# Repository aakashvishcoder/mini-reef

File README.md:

# Mini-Reef FPGA Board

A low-cost 4-layer Artix-7 board that runs a small Reef-style accelerator against real HyperRAM, and measures bandwidth, latency and tokens per second. A CH32V307 board acts as the test host.

- FPGA: XC7A15T-FTG256 (footprint-compatible with XC7A35T)
- Memory: Winbond W958D8NBYA5I, 256 Mb HyperRAM on a 1.8 V bank
- USB-C: power, plus CH347T for USB-JTAG and console
- Manufacturing: JLCPCB 4-layer, assembled

## Layout

| Path | Contents |
|---|---|
| `schematic-guide/` | Section-by-section schematic guides |
| `planning-BOM.csv` | Planning BOM with LCSC numbers (not the JLC upload format) |
| `mini-reef.pretty/` | Project footprints not in KiCad's stock library |
| `mini-reef.kicad_sym` | Project symbols: CH347T, W958D8NBYA HyperRAM |
| `fp-lib-table`, `sym-lib-table` | Register the project libraries |

## Schematic sections

| # | Section | Main parts |
|---|---|---|
| 1 | USB-C & Power | USB-C, fuse, 3x TPS62130A (1.0 / 1.8 / 3.3 V, sequenced) |
| 2 | FPGA Power | XC7A15T unit D, UG483 decoupling |
| 3 | HyperRAM | W958D8NBYA5I on bank 35 (1.8 V), debug pins on bank 34 |
| 4 | USB-JTAG & Console | CH347T (mode 3), JTAG header, bank 0 config straps |
| 5 | Clock & Config | 50 MHz oscillator, W25Q32 flash, banks 14/15 |
| 6 | Test Host & Debug | CH32V307 link header, debug header, LEDs, button |

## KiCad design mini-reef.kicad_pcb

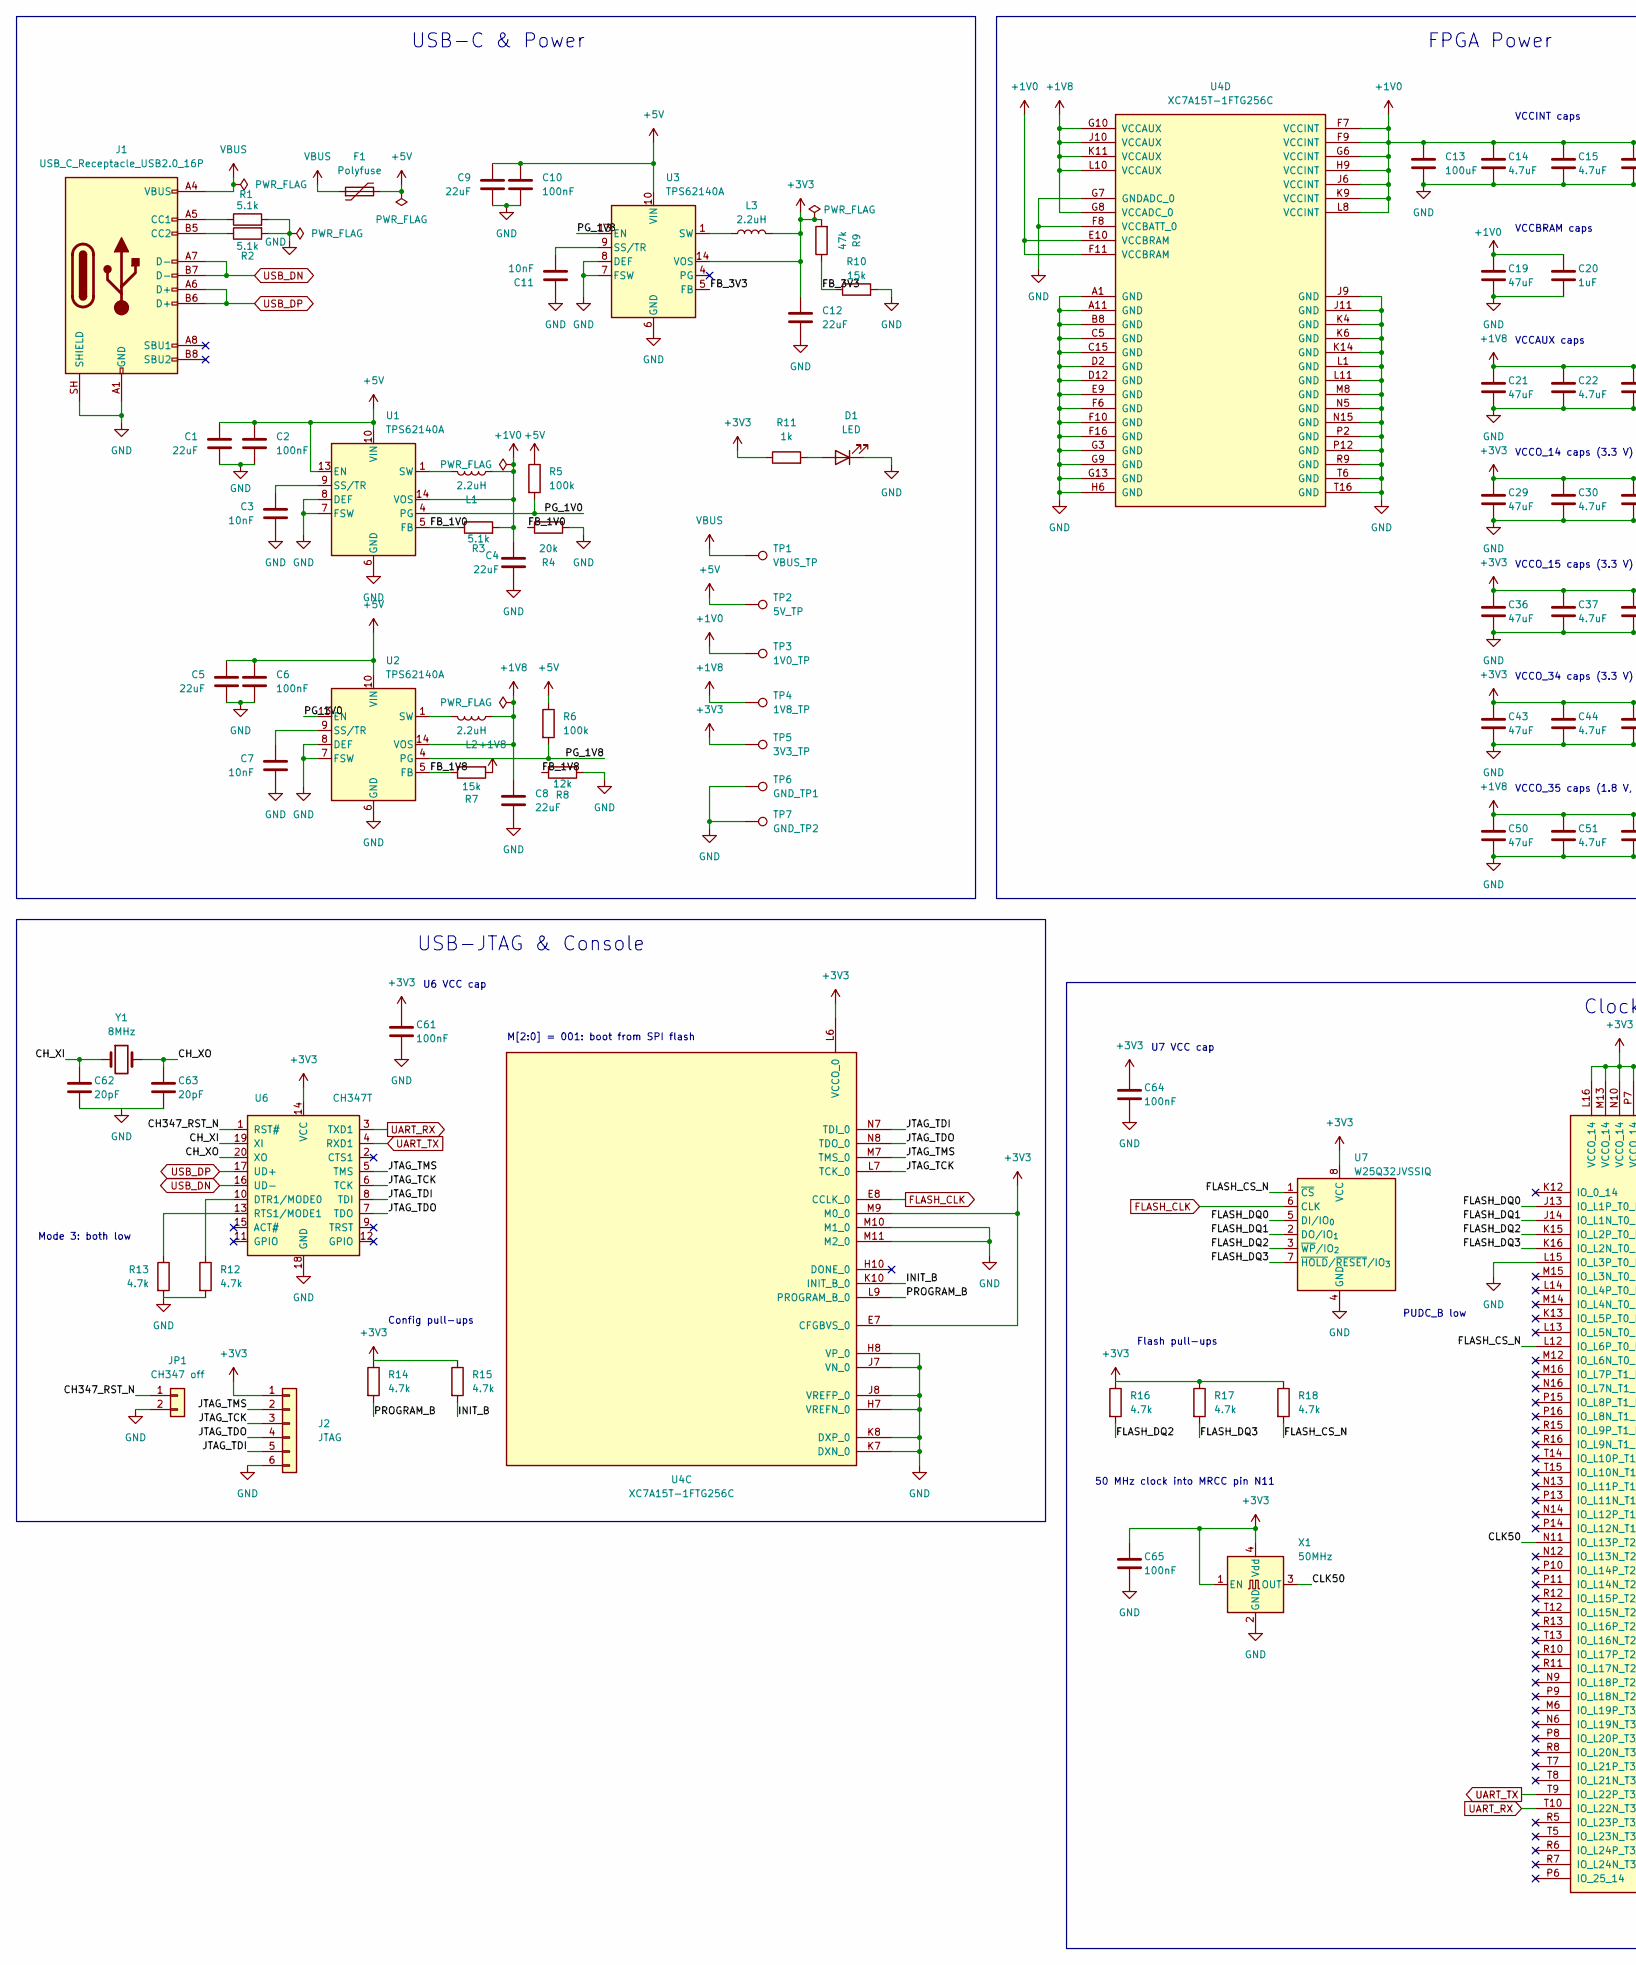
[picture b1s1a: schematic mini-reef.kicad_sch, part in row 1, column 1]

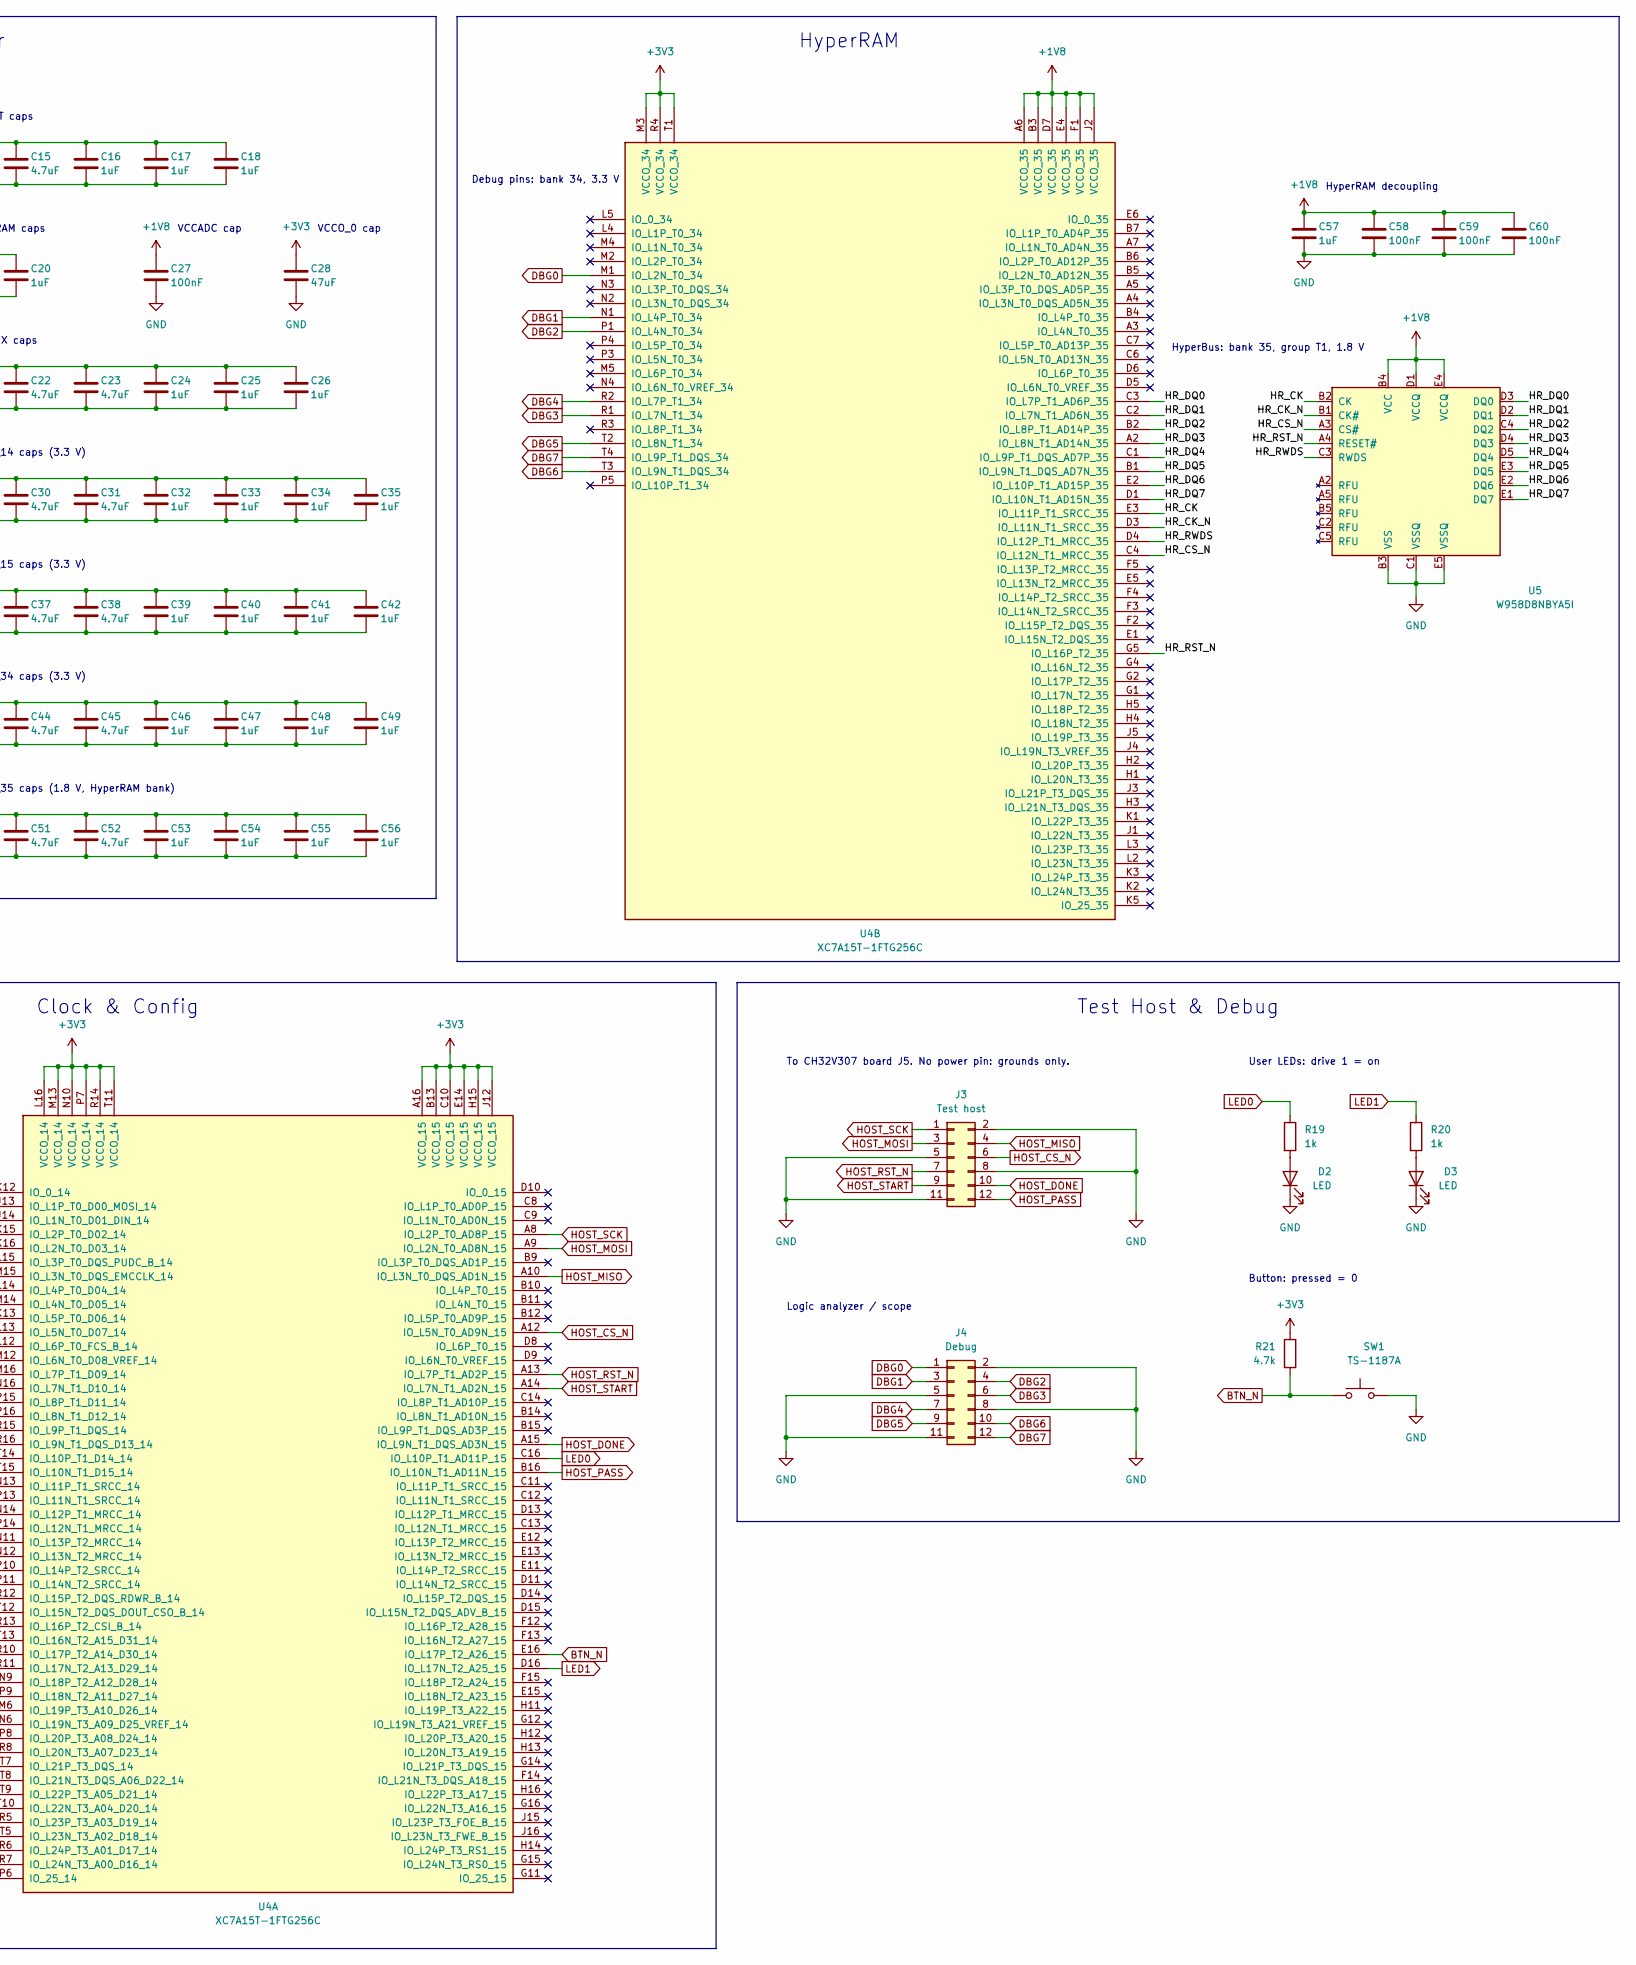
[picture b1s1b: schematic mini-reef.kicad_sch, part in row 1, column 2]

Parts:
C1, C4, C5, C8, C9, C12: 22uF; C_0805_2012Metric; LCSC C45783
C2, C6, C10, C27, C58, C59, C60, C61, C64, C65: 100nF; C_0402_1005Metric; LCSC C1525
C3, C7, C11: 10nF; C_0402_1005Metric; LCSC C15195
C13: 100uF; C_1206_3216Metric; LCSC C15008
C14, C15, C22, C23, C30, C31, C37, C38, C44, C45, C51, C52: 4.7uF; C_0805_2012Metric; LCSC C1779
C16, C17, C18, C20, C24, C25, C26, C32, C33, C34, C35, C39, C40, C41, C42, C46, C47, C48, C49, C53, C54, C55, C56, C57: 1uF; C_0402_1005Metric; LCSC C52923
C19, C21, C28, C29, C36, C43, C50: 47uF; C_1206_3216Metric; LCSC C96123
C62, C63: 20pF; C_0402_1005Metric; LCSC C1554
D1, D2, D3: LED; LED_0603_1608Metric; LCSC C2286
F1: Polyfuse; Fuse_1206_3216Metric; LCSC C20801
J1: USB_C_Receptacle_USB2.0_16P; USB_C_Receptacle_HRO_TYPE-C-31-M-12; LCSC C165948
J2: JTAG; PinHeader_1x06_P2.54mm_Vertical
J3: Test host; PinHeader_2x06_P2.54mm_Vertical
J4: Debug; PinHeader_2x06_P2.54mm_Vertical
JP1: CH347 off; PinHeader_1x02_P2.54mm_Vertical
L1, L2, L3: 2.2uH; IND-SMD_L4.5-W4.1_SRP4020TA; LCSC C719179
R1, R2, R3: 5.1k; R_0402_1005Metric; LCSC C25905
R4: 20k; R_0402_1005Metric; LCSC C25765
R5, R6: 100k; R_0402_1005Metric; LCSC C25741
R7, R10: 15k; R_0402_1005Metric; LCSC C25756
R8: 12k; R_0402_1005Metric; LCSC C25752
R9: 47k; R_0402_1005Metric; LCSC C25792
R11, R19, R20: 1k; R_0402_1005Metric; LCSC C11702
R12, R13, R14, R15, R16, R17, R18, R21: 4.7k; R_0402_1005Metric; LCSC C25900
SW1: TS-1187A; SW_Push_1P1T_XKB_TS-1187A; LCSC C318884
TP1: VBUS_TP; TestPoint_Pad_D1.5mm
TP2: 5V_TP; TestPoint_Pad_D1.5mm
TP3: 1V0_TP; TestPoint_Pad_D1.5mm
TP4: 1V8_TP; TestPoint_Pad_D1.5mm
TP5: 3V3_TP; TestPoint_Pad_D1.5mm
TP6: GND_TP1; TestPoint_Pad_D1.5mm
TP7: GND_TP2; TestPoint_Pad_D1.5mm
U1, U2, U3: TPS62140A; VQFN-16-1EP_3x3mm_P0.5mm_EP1.68x1.68mm_ThermalVias; LCSC C129366
U4: XC7A15T-1FTG256C; Xilinx_FTG256; LCSC C1521788
U5: W958D8NBYA5I; BGA-24_6x8mm_Layout5x5_P1.0mm; LCSC C7420405
U6: CH347T; TSSOP-20_4.4x6.5mm_P0.65mm; LCSC C5122332
U7: W25Q32JVSSIQ; SOIC-8_5.3x5.3mm_P1.27mm; LCSC C179173
X1: 50MHz; Oscillator_SMD_Abracon_ASE-4Pin_3.2x2.5mm; LCSC C717684
Y1: 8MHz; Crystal_SMD_5032-2Pin_5.0x3.2mm; LCSC C115962

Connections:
+1V0: C4.1, C13.1, C14.1, C15.1, C16.1, C17.1, C18.1, C19.1, C20.1, L1.2, R3.2, TP3.1, U1.14 (VOS), U4.E10 (VCCBRAM), U4.F7 (VCCINT), U4.F9 (VCCINT), U4.F11 (VCCBRAM), U4.G6 (VCCINT), U4.H9 (VCCINT), U4.J6 (VCCINT), U4.K9 (VCCINT), U4.L8 (VCCINT)
+1V8: C8.1, C21.1, C22.1, C23.1, C24.1, C25.1, C26.1, C27.1, C50.1, C51.1, C52.1, C53.1, C54.1, C55.1, C56.1, C57.1, C58.1, C59.1, C60.1, L2.2, R7.2, TP4.1, U2.14 (VOS), U4.A6 (VCCO_35), U4.B3 (VCCO_35), U4.D7 (VCCO_35), U4.E4 (VCCO_35), U4.F1 (VCCO_35), U4.G8 (VCCADC_0), U4.G10 (VCCAUX), U4.J2 (VCCO_35), U4.J10 (VCCAUX), U4.K11 (VCCAUX), U4.L10 (VCCAUX), U5.B4 (VCC), U5.D1 (VCCQ), U5.E4 (VCCQ)
+3V3: C12.1, C28.1, C29.1, C30.1, C31.1, C32.1, C33.1, C34.1, C35.1, C36.1, C37.1, C38.1, C39.1, C40.1, C41.1, C42.1, C43.1, C44.1, C45.1, C46.1, C47.1, C48.1, C49.1, C61.1, C64.1, C65.1, J2.1, L3.2, R9.2, R11.1, R14.1, R15.1, R16.1, R17.1, R18.1, R21.1, TP5.1, U3.14 (VOS), U4.A16 (VCCO_15), U4.B13 (VCCO_15), U4.C10 (VCCO_15), U4.E7 (CFGBVS_0), U4.E14 (VCCO_15), U4.H15 (VCCO_15), U4.J12 (VCCO_15), U4.L6 (VCCO_0), U4.L16 (VCCO_14), U4.M3 (VCCO_34), U4.M9 (M0_0), U4.M13 (VCCO_14), U4.N10 (VCCO_14), U4.P7 (VCCO_14), U4.R4 (VCCO_34), U4.R14 (VCCO_14), U4.T1 (VCCO_34), U4.T11 (VCCO_14), U6.14 (VCC), U7.8 (VCC), X1.1 (EN), X1.4 (Vdd)
+5V: C1.1, C2.1, C5.1, C6.1, C9.1, C10.1, F1.2, R5.1, R6.1, TP2.1, U1.10 (VIN), U1.11 (VIN), U1.12 (VIN), U1.13 (EN), U2.10 (VIN), U2.11 (VIN), U2.12 (VIN), U3.10 (VIN), U3.11 (VIN), U3.12 (VIN)
/CH347_RST_N: JP1.1, U6.1 (RST#)
/CH_XI: C62.1, U6.19 (XI), Y1.1
/CH_XO: C63.1, U6.20 (XO), Y1.2
/CLK50: U4.N11 (IO_L13P_T2_MRCC_14), X1.3 (OUT)
/FB_1V0: R3.1, R4.1, U1.5 (FB)
/FB_1V8: R7.1, R8.2, U2.5 (FB)
/FB_3V3: R9.1, R10.1, U3.5 (FB)
/FLASH_CS_N: R18.2, U4.L12 (IO_L6P_T0_FCS_B_14), U7.1 (~CS)
/FLASH_DQ0: U4.J13 (IO_L1P_T0_D00_MOSI_14), U7.5 (DI/IO_{0})
/FLASH_DQ1: U4.J14 (IO_L1N_T0_D01_DIN_14), U7.2 (DO/IO_{1})
/FLASH_DQ2: R16.2, U4.K15 (IO_L2P_T0_D02_14), U7.3 (~WP/IO_{2})
/FLASH_DQ3: R17.2, U4.K16 (IO_L2N_T0_D03_14), U7.7 (~HOLD/~RESET/IO_{3})
/HR_CK: U4.E3 (IO_L11P_T1_SRCC_35), U5.B2 (CK)
/HR_CK_N: U4.D3 (IO_L11N_T1_SRCC_35), U5.B1 (CK#)
/HR_CS_N: U4.C4 (IO_L12N_T1_MRCC_35), U5.A3 (CS#)
/HR_DQ0: U4.C3 (IO_L7P_T1_AD6P_35), U5.D3 (DQ0)
/HR_DQ1: U4.C2 (IO_L7N_T1_AD6N_35), U5.D2 (DQ1)
/HR_DQ2: U4.B2 (IO_L8P_T1_AD14P_35), U5.C4 (DQ2)
/HR_DQ3: U4.A2 (IO_L8N_T1_AD14N_35), U5.D4 (DQ3)
/HR_DQ4: U4.C1 (IO_L9P_T1_DQS_AD7P_35), U5.D5 (DQ4)
/HR_DQ5: U4.B1 (IO_L9N_T1_DQS_AD7N_35), U5.E3 (DQ5)
/HR_DQ6: U4.E2 (IO_L10P_T1_AD15P_35), U5.E2 (DQ6)
/HR_DQ7: U4.D1 (IO_L10N_T1_AD15N_35), U5.E1 (DQ7)
/HR_RST_N: U4.G5 (IO_L16P_T2_35), U5.A4 (RESET#)
/HR_RWDS: U4.D4 (IO_L12P_T1_MRCC_35), U5.C3 (RWDS)
/INIT_B: R15.2, U4.K10 (INIT_B_0)
/JTAG_TCK: J2.3, U4.L7 (TCK_0), U6.6 (TCK)
/JTAG_TDI: J2.5, U4.N7 (TDI_0), U6.8 (TDI)
/JTAG_TDO: J2.4, U4.N8 (TDO_0), U6.7 (TDO)
/JTAG_TMS: J2.2, U4.M7 (TMS_0), U6.5 (TMS)
/PG_1V0: R5.2, U1.4 (PG), U2.13 (EN)
/PG_1V8: R6.2, U2.4 (PG), U3.13 (EN)
/PROGRAM_B: R14.2, U4.L9 (PROGRAM_B_0)
BTN_N: R21.2, SW1.1, U4.E16 (IO_L17P_T2_A26_15)
DBG0: J4.1, U4.M1 (IO_L2N_T0_34)
DBG1: J4.3, U4.N1 (IO_L4P_T0_34)
DBG2: J4.4, U4.P1 (IO_L4N_T0_34)
DBG3: J4.6, U4.R1 (IO_L7N_T1_34)
DBG4: J4.7, U4.R2 (IO_L7P_T1_34)
DBG5: J4.9, U4.T2 (IO_L8N_T1_34)
DBG6: J4.10, U4.T3 (IO_L9N_T1_DQS_34)
DBG7: J4.12, U4.T4 (IO_L9P_T1_DQS_34)
FLASH_CLK: U4.E8 (CCLK_0), U7.6 (CLK)
GND: C1.2, C2.2, C3.2, C4.2, C5.2, C6.2, C7.2, C8.2, C9.2, C10.2, C11.2, C12.2, C13.2, C14.2, C15.2, C16.2, C17.2, C18.2, C19.2, C20.2, C21.2, C22.2, C23.2, C24.2, C25.2, C26.2, C27.2, C28.2, C29.2, C30.2, C31.2, C32.2, C33.2, C34.2, C35.2, C36.2, C37.2, C38.2, C39.2, C40.2, C41.2, C42.2, C43.2, C44.2, C45.2, C46.2, C47.2, C48.2, C49.2, C50.2, C51.2, C52.2, C53.2, C54.2, C55.2, C56.2, C57.2, C58.2, C59.2, C60.2, C61.2, C62.2, C63.2, C64.2, C65.2, D1.1 (K), D2.1 (K), D3.1 (K), J1.A1 (GND), J1.A12 (GND), J1.B1 (GND), J1.B12 (GND), J1.SH (SHIELD), J2.6, J3.2, J3.5, J3.8, J3.11, J4.2, J4.5, J4.8, J4.11, JP1.2, R1.2, R2.2, R4.2, R8.1, R10.2, R12.2, R13.2, SW1.2, TP6.1, TP7.1, U1.6 (GND), U1.7 (FSW), U1.8 (DEF), U1.15 (GND), U1.16 (GND), U1.17 (GND), U2.6 (GND), U2.7 (FSW), U2.8 (DEF), U2.15 (GND), U2.16 (GND), U2.17 (GND), U3.6 (GND), U3.7 (FSW), U3.8 (DEF), U3.15 (GND), U3.16 (GND), U3.17 (GND), U4.A1 (GND), U4.A11 (GND), U4.B8 (GND), U4.C5 (GND), U4.C15 (GND), U4.D2 (GND), U4.D12 (GND), U4.E9 (GND), U4.F6 (GND), U4.F8 (VCCBATT_0), U4.F10 (GND), U4.F16 (GND), U4.G3 (GND), U4.G7 (GNDADC_0), U4.G9 (GND), U4.G13 (GND), U4.H6 (GND), U4.H7 (VREFN_0), U4.H8 (VP_0), U4.J7 (VN_0), U4.J8 (VREFP_0), U4.J9 (GND), U4.J11 (GND), U4.K4 (GND), U4.K6 (GND), U4.K7 (DXN_0), U4.K8 (DXP_0), U4.K14 (GND), U4.L1 (GND), U4.L11 (GND), U4.L15 (IO_L3P_T0_DQS_PUDC_B_14), U4.M8 (GND), U4.M10 (M1_0), U4.M11 (M2_0), U4.N5 (GND), U4.N15 (GND), U4.P2 (GND), U4.P12 (GND), U4.R9 (GND), U4.T6 (GND), U4.T16 (GND), U5.B3 (VSS), U5.C1 (VSSQ), U5.E5 (VSSQ), U6.18 (GND), U7.4 (GND), X1.2 (GND)
HOST_CS_N: J3.6, U4.A12 (IO_L5N_T0_AD9N_15)
HOST_DONE: J3.10, U4.A15 (IO_L9N_T1_DQS_AD3N_15)
HOST_MISO: J3.4, U4.A10 (IO_L3N_T0_DQS_AD1N_15)
HOST_MOSI: J3.3, U4.A9 (IO_L2N_T0_AD8N_15)
HOST_PASS: J3.12, U4.B16 (IO_L10N_T1_AD11N_15)
HOST_RST_N: J3.7, U4.A13 (IO_L7P_T1_AD2P_15)
HOST_SCK: J3.1, U4.A8 (IO_L2P_T0_AD8P_15)
HOST_START: J3.9, U4.A14 (IO_L7N_T1_AD2N_15)
LED0: R19.1, U4.C16 (IO_L10P_T1_AD11P_15)
LED1: R20.1, U4.D16 (IO_L17N_T2_A25_15)
unnamed: D1.2 (A), R11.2
unnamed: D2.2 (A), R19.2
unnamed: D3.2 (A), R20.2
unnamed: J1.A5 (CC1), R1.1
unnamed: J1.B5 (CC2), R2.1
unnamed: L1.1, U1.1 (SW), U1.2 (SW), U1.3 (SW)
unnamed: L2.1, U2.1 (SW), U2.2 (SW), U2.3 (SW)
unnamed: L3.1, U3.1 (SW), U3.2 (SW), U3.3 (SW)
unnamed: C3.1, U1.9 (SS/TR)
unnamed: C7.1, U2.9 (SS/TR)
unnamed: C11.1, U3.9 (SS/TR)
unnamed: R12.1, U6.10 (DTR1/MODE0)
unnamed: R13.1, U6.13 (RTS1/MODE1)
UART_RX: U4.T10 (IO_L22N_T3_A04_D20_14), U6.3 (TXD1)
UART_TX: U4.T9 (IO_L22P_T3_A05_D21_14), U6.4 (RXD1)
USB_DN: J1.A7 (D-), J1.B7 (D-), U6.16 (UD-)
USB_DP: J1.A6 (D+), J1.B6 (D+), U6.17 (UD+)
VBUS: F1.1, J1.A4 (VBUS), J1.A9 (VBUS), J1.B4 (VBUS), J1.B9 (VBUS), TP1.1

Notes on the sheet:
USB-C & Power
VCCINT caps
VCCBRAM caps
VCCADC cap
VCCO_0 cap
VCCAUX caps
VCCO_14 caps (3.3 V)
VCCO_15 caps (3.3 V)
VCCO_34 caps (3.3 V)
VCCO_35 caps (1.8 V, HyperRAM bank)
HyperRAM decoupling
HyperBus: bank 35, group T1, 1.8 V
Debug pins: bank 34, 3.3 V
HyperRAM
FPGA Power
Mode 3: both low
U6 VCC cap
M[2:0] = 001: boot from SPI flash
Config pull-ups
USB-JTAG & Console
PUDC_B low
U7 VCC cap
Flash pull-ups
50 MHz clock into MRCC pin N11
Clock & Config
To CH32V307 board J5. No power pin: grounds only.
Logic analyzer / scope
User LEDs: drive 1 = on
Button: pressed = 0
Test Host & Debug

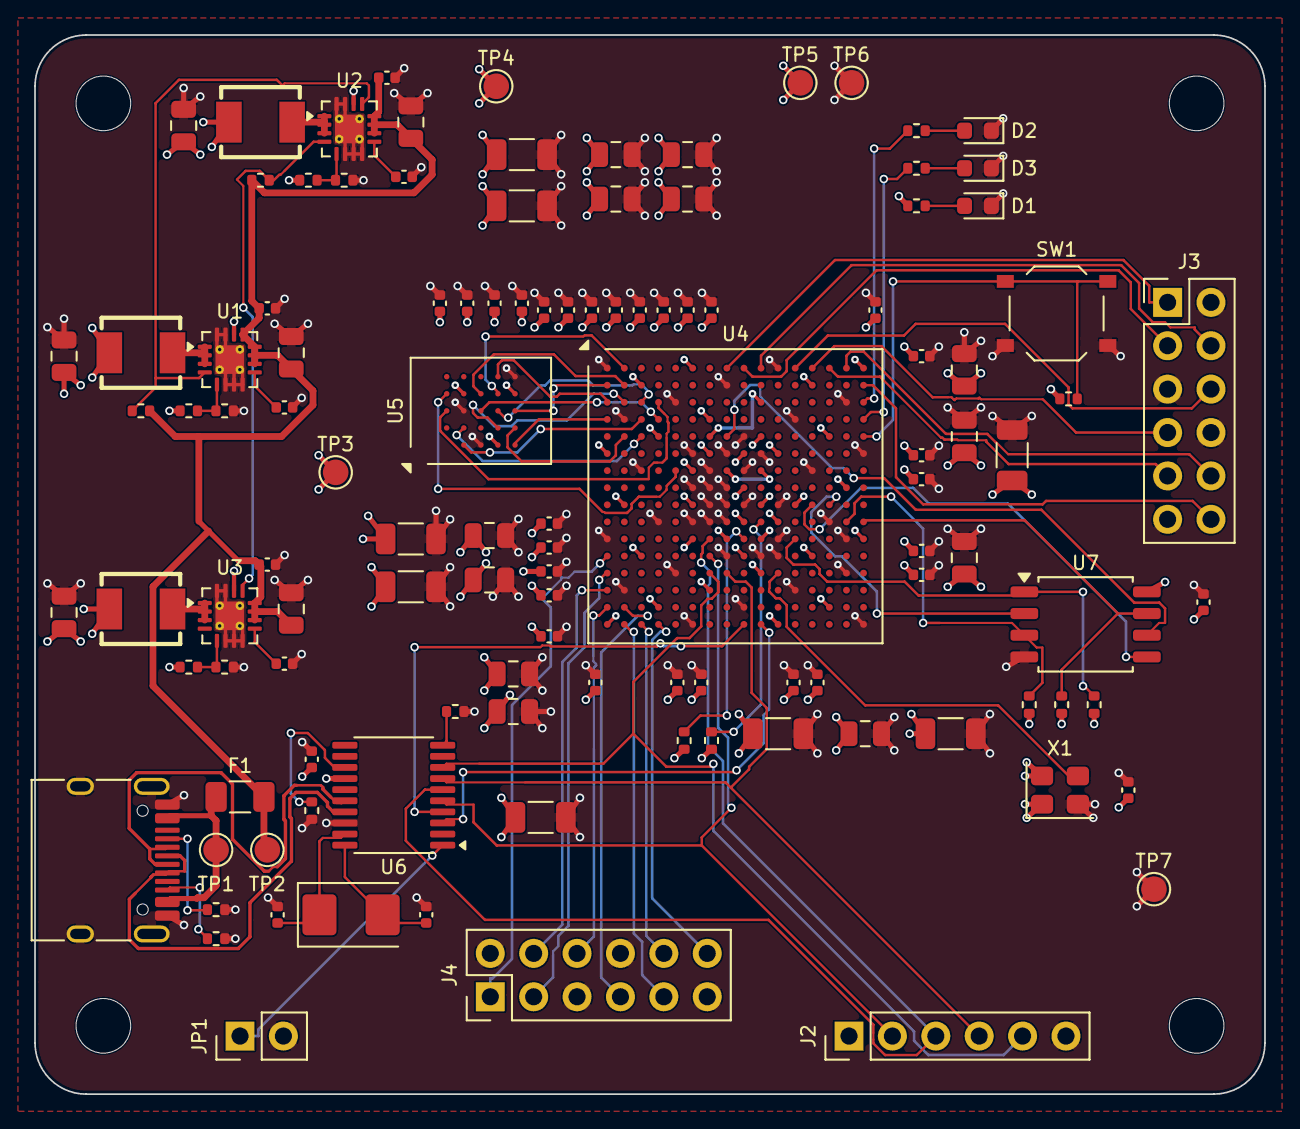
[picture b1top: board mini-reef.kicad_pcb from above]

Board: 4 copper layers, 72.0 x 62.0 mm, 119 parts (0 on the bottom side), 76 nets.

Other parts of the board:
H1, H2, H3, H4: MountingHole_3.2mm_M3

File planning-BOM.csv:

Section,Ref,Qty/board,Value,Manufacturer Part,LCSC #,JLC Type,KiCad Symbol,KiCad Footprint,Notes
1 USB-C & Power,J1,1,USB-C receptacle USB2.0 16-pin,TYPE-C-31-M-12 (HRO),C165948,Extended,Connector:USB_C_Receptacle_USB2.0_16P,Connector_USB:USB_C_Receptacle_HRO_TYPE-C-31-M-12,Quoted on the RISC-V board order
1 USB-C & Power,F1,1,PTC fuse 1.1A hold 6V 1206,SMD1206P110TF (RUILON),C20801,Extended,Device:Polyfuse,Fuse:Fuse_1206_3216Metric,
1 USB-C & Power,"R1,R2,R3",3,5.1k 1% 0402,0402WGF5101TCE,C25905,Basic,Device:R,Resistor_SMD:R_0402_1005Metric,CC pull-downs; R3 = 1V0 FB top
1 USB-C & Power,"U1,U2,U3",3,2A buck regulator,TPS62140ARGTR (TI),C129366,Extended,Regulator_Switching:TPS62130A,Package_DFN_QFN:VQFN-16-1EP_3x3mm_P0.5mm_EP1.68x1.68mm_ThermalVias,Must be the A version: PG low while disabled. Pin-compatible with TPS62130A (out of stock at JLC 2026-11-12)
1 USB-C & Power,"L1,L2,L3",3,2.2uH power inductor,SRP4020TA-2R2M (Bourns),C719179,Extended,Device:L,mini-reef:IND-SMD_L4.5-W4.1_SRP4020TA,Footprint in project library
1 USB-C & Power,"C1,C4,C5,C8,C9,C12",6,22uF 25V X5R 0805,CL21A226MAQNNNE,C45783,Basic,Device:C,Capacitor_SMD:C_0805_2012Metric,Regulator input and output
1 USB-C & Power,"C2,C6,C10",3,100nF 16V X7R 0402,CL05B104KO5NNNC,C1525,Basic,Device:C,Capacitor_SMD:C_0402_1005Metric,AVIN decoupling
1 USB-C & Power,"C3,C7,C11",3,10nF 50V X7R 0402,CL05B103KB5NNNC,C15195,Basic,Device:C,Capacitor_SMD:C_0402_1005Metric,Soft-start 5 ms
1 USB-C & Power,R4,1,20k 1% 0402,0402WGF2002TCE,C25765,Basic,Device:R,Resistor_SMD:R_0402_1005Metric,1V0 FB bottom
1 USB-C & Power,"R5,R6",2,100k 1% 0402,0402WGF1003TCE,C25741,Basic,Device:R,Resistor_SMD:R_0402_1005Metric,PG pull-ups
1 USB-C & Power,"R7,R10",2,15k 1% 0402,0402WGF1502TCE,C25756,Basic,Device:R,Resistor_SMD:R_0402_1005Metric,1V8 FB top; 3V3 FB bottom
1 USB-C & Power,R8,1,12k 1% 0402,0402WGF1202TCE,C25752,Basic,Device:R,Resistor_SMD:R_0402_1005Metric,1V8 FB bottom
1 USB-C & Power,R9,1,47k 1% 0402,0402WGF4702TCE,C25792,Basic,Device:R,Resistor_SMD:R_0402_1005Metric,3V3 FB top
1 USB-C & Power,R11,1,1k 1% 0402,0402WGF1001TCE,C11702,Basic,Device:R,Resistor_SMD:R_0402_1005Metric,Power LED
1 USB-C & Power,D1,1,Red LED 0603,KT-0603R,C2286,Basic,Device:LED,LED_SMD:LED_0603_1608Metric,All rails good
1 USB-C & Power,TP1-TP7,7,Test points,-,-,-,Connector:TestPoint,TestPoint:TestPoint_Pad_D1.5mm,Copper pads; exclude from BOM
2 FPGA Power,U4,1,Artix-7 FPGA FTG256 (XC7A35T-1FTG256C is drop-in),XC7A15T-1FTG256C (AMD),C1521788,Extended,FPGA_Xilinx_Artix7:XC7A15T-FTG256,Package_BGA:Xilinx_FTG256,X-ray required; check stock (cached listing showed 6)
2 FPGA Power,C13,1,100uF 6.3V X5R 1206,CL31A107MQHNNNE,C15008,Basic,Device:C,Capacitor_SMD:C_1206_3216Metric,VCCINT bulk
2 FPGA Power,"C19,C21,C28,C29,C36,C43,C50",7,47uF 10V X5R 1206,CL31A476MPHNNNE,C96123,Basic,Device:C,Capacitor_SMD:C_1206_3216Metric,Bulk: VCCBRAM VCCAUX VCCO_0/14/15/34/35
2 FPGA Power,"C14,C15,C22,C23,C30,C31,C37,C38,C44,C45,C51,C52",12,4.7uF 25V X5R 0805,CL21A475KAQNNNE,C1779,Basic,Device:C,Capacitor_SMD:C_0805_2012Metric,UG483 mid-frequency
2 FPGA Power,"C16,C17,C18,C20,C24,C25,C26,C32,C33,C34,C35,C39,C40,C41,C42,C46,C47,C48,C49,C53,C54,C55,C56",23,1uF 25V X5R 0402,CL05A105KA5NQNC,C52923,Basic,Device:C,Capacitor_SMD:C_0402_1005Metric,UG483 0.47uF slots (>=0.47uF allowed)
"2,3,4,5 small decoupling","C27,C58,C59,C60,C61,C64,C65",7,100nF 16V X7R 0402,CL05B104KO5NNNC,C1525,Basic,Device:C,Capacitor_SMD:C_0402_1005Metric,VCCADC; HyperRAM; CH347; flash; oscillator
3 HyperRAM,U5,1,256Mb HyperRAM 1.8V x8 HyperBus,W958D8NBYA5I (Winbond),C7420405,Extended,mini-reef:W958D8NBYA,Package_BGA:BGA-24_6x8mm_Layout5x5_P1.0mm,Symbol in project library; X-ray required
3 HyperRAM,C57,1,1uF 0402,CL05A105KA5NQNC,C52923,Basic,Device:C,Capacitor_SMD:C_0402_1005Metric,HyperRAM bulk (same line as section 2 1uF)
4 USB-JTAG,U6,1,USB 2.0 HS to UART + JTAG (mode 3),CH347T (WCH),C5122332,Extended,mini-reef:CH347T,Package_SO:TSSOP-20_4.4x6.5mm_P0.65mm,Symbol in project library
4 USB-JTAG,Y1,1,8MHz crystal 5032,X50328MSB2GI (YXC),C115962,Basic,Device:Crystal,Crystal:Crystal_SMD_5032-2Pin_5.0x3.2mm,Same as RISC-V board Y2
4 USB-JTAG,"C62,C63",2,20pF C0G 0402,0402CG200J500NT,C1554,Basic,Device:C,Capacitor_SMD:C_0402_1005Metric,Crystal load
"4,5,6 pull resistors","R12,R13,R14,R15,R16,R17,R18,R21",8,4.7k 1% 0402,0402WGF4701TCE,C25900,Basic,Device:R,Resistor_SMD:R_0402_1005Metric,CH347 mode; PROGRAM_B; INIT_B; flash WP/HOLD/CS; button
4 USB-JTAG,J2,1,JTAG header 1x6 2.54mm,-,-,Hand-solder,Connector_Generic:Conn_01x06,Connector_PinHeader_2.54mm:PinHeader_1x06_P2.54mm_Vertical,Exclude from BOM
4 USB-JTAG,JP1,1,Jumper 1x2 2.54mm (CH347 reset),-,-,Hand-solder,Connector_Generic:Conn_01x02,Connector_PinHeader_2.54mm:PinHeader_1x02_P2.54mm_Vertical,Exclude from BOM
5 Clock & Config,U7,1,32Mbit SPI flash,W25Q32JVSSIQ (Winbond),C179173,Extended,Memory_Flash:W25Q32JVSS,Package_SO:SOIC-8_5.3x5.3mm_P1.27mm,Holds ~17.5 Mbit bitstream
5 Clock & Config,X1,1,50MHz oscillator 3.3V 3225,OT322550MJBA4SL (YXC),C717684,Extended,Oscillator:ASE-xxxMHz,Oscillator:Oscillator_SMD_Abracon_ASE-4Pin_3.2x2.5mm,Into MRCC pin N11
6 Test Host & Debug,"J3,J4",2,2x6 2.54mm header,-,-,Hand-solder,Connector_Generic:Conn_02x06_Odd_Even,Connector_PinHeader_2.54mm:PinHeader_2x06_P2.54mm_Vertical,Exclude from BOM; snap from one 2x40 strip
6 Test Host & Debug,"D2,D3",2,Red LED 0603,KT-0603R,C2286,Basic,Device:LED,LED_SMD:LED_0603_1608Metric,User LEDs (same line as D1)
6 Test Host & Debug,"R19,R20",2,1k 1% 0402,0402WGF1001TCE,C11702,Basic,Device:R,Resistor_SMD:R_0402_1005Metric,LED resistors (same line as R11)
6 Test Host & Debug,SW1,1,Tactile switch 5.1x5.1mm,TS-1187A-B-A-B (XKB),C318884,Basic,Switch:SW_Push,Button_Switch_SMD:SW_Push_1P1T_XKB_TS-1187A,User/reset button
,,,,,,,,,
SUMMARY (cached prices; confirm at JLC quote),,,,,,,,,
Extended part types,9,,"TPS62140A, inductor, USB-C, fuse, FPGA, HyperRAM, CH347T, flash, oscillator",,,,,,~$27 in JLC loading fees
Parts per board,~$27.50,,,,,,,,FPGA ~$14.30 + HyperRAM ~$4.50 + CH347T ~$3.30 + power ~$3.70 + rest ~$1.70
Estimated all-in for 2 assembled boards,~$220,,,,,,,,Incl. setup/stencil ~$37; 5 PCBs ~$10; ~35% tariff; DDP shipping. XC7A35T@$40 -> ~$290

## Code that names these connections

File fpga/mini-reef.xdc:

# Mini-Reef pin constraints for XC7A15T-1FTG256C (XC7A35T is pin-compatible).
# Generated by fpga/gen_xdc.py from the KiCad netlist. Regenerate if the schematic changes.

# Configuration: bank 0 and bank 14 are 3.3 V, boot is Master SPI x4 from the W25Q32.
set_property CFGBVS VCCO [current_design]
set_property CONFIG_VOLTAGE 3.3 [current_design]
set_property BITSTREAM.CONFIG.SPI_BUSWIDTH 4 [current_design]
set_property CONFIG_MODE SPIx4 [current_design]

# 50 MHz clock (bank 14, MRCC)
set_property -dict {PACKAGE_PIN N11 IOSTANDARD LVCMOS33} [get_ports {clk50}]  ;# IO_L13P_T2_MRCC_14
create_clock -name clk50 -period 20.000 [get_ports {clk50}]

# HyperRAM, HyperBus (bank 35, byte group T1, 1.8 V)
set_property -dict {PACKAGE_PIN E3  IOSTANDARD LVCMOS18} [get_ports {hr_ck}]  ;# IO_L11P_T1_SRCC_35
set_property -dict {PACKAGE_PIN D3  IOSTANDARD LVCMOS18} [get_ports {hr_ck_n}]  ;# IO_L11N_T1_SRCC_35
set_property -dict {PACKAGE_PIN C4  IOSTANDARD LVCMOS18} [get_ports {hr_cs_n}]  ;# IO_L12N_T1_MRCC_35
set_property -dict {PACKAGE_PIN D4  IOSTANDARD LVCMOS18} [get_ports {hr_rwds}]  ;# IO_L12P_T1_MRCC_35
set_property -dict {PACKAGE_PIN G5  IOSTANDARD LVCMOS18} [get_ports {hr_rst_n}]  ;# IO_L16P_T2_35
set_property -dict {PACKAGE_PIN C3  IOSTANDARD LVCMOS18} [get_ports {hr_dq[0]}]  ;# IO_L7P_T1_AD6P_35
set_property -dict {PACKAGE_PIN C2  IOSTANDARD LVCMOS18} [get_ports {hr_dq[1]}]  ;# IO_L7N_T1_AD6N_35
set_property -dict {PACKAGE_PIN B2  IOSTANDARD LVCMOS18} [get_ports {hr_dq[2]}]  ;# IO_L8P_T1_AD14P_35
set_property -dict {PACKAGE_PIN A2  IOSTANDARD LVCMOS18} [get_ports {hr_dq[3]}]  ;# IO_L8N_T1_AD14N_35
set_property -dict {PACKAGE_PIN C1  IOSTANDARD LVCMOS18} [get_ports {hr_dq[4]}]  ;# IO_L9P_T1_DQS_AD7P_35
set_property -dict {PACKAGE_PIN B1  IOSTANDARD LVCMOS18} [get_ports {hr_dq[5]}]  ;# IO_L9N_T1_DQS_AD7N_35
set_property -dict {PACKAGE_PIN E2  IOSTANDARD LVCMOS18} [get_ports {hr_dq[6]}]  ;# IO_L10P_T1_AD15P_35
set_property -dict {PACKAGE_PIN D1  IOSTANDARD LVCMOS18} [get_ports {hr_dq[7]}]  ;# IO_L10N_T1_AD15N_35

# Console UART to CH347T (bank 14). Named from the FPGA side.
set_property -dict {PACKAGE_PIN T9  IOSTANDARD LVCMOS33} [get_ports {uart_tx}]  ;# IO_L22P_T3_A05_D21_14
set_property -dict {PACKAGE_PIN T10 IOSTANDARD LVCMOS33} [get_ports {uart_rx}]  ;# IO_L22N_T3_A04_D20_14

# Test host link to the CH32V307 board, J3 (bank 15)
set_property -dict {PACKAGE_PIN A8  IOSTANDARD LVCMOS33} [get_ports {host_sck}]  ;# IO_L2P_T0_AD8P_15
set_property -dict {PACKAGE_PIN A9  IOSTANDARD LVCMOS33} [get_ports {host_mosi}]  ;# IO_L2N_T0_AD8N_15
set_property -dict {PACKAGE_PIN A10 IOSTANDARD LVCMOS33} [get_ports {host_miso}]  ;# IO_L3N_T0_DQS_AD1N_15
set_property -dict {PACKAGE_PIN A12 IOSTANDARD LVCMOS33} [get_ports {host_cs_n}]  ;# IO_L5N_T0_AD9N_15
set_property -dict {PACKAGE_PIN A13 IOSTANDARD LVCMOS33} [get_ports {host_rst_n}]  ;# IO_L7P_T1_AD2P_15
set_property -dict {PACKAGE_PIN A14 IOSTANDARD LVCMOS33} [get_ports {host_start}]  ;# IO_L7N_T1_AD2N_15
set_property -dict {PACKAGE_PIN A15 IOSTANDARD LVCMOS33} [get_ports {host_done}]  ;# IO_L9N_T1_DQS_AD3N_15
set_property -dict {PACKAGE_PIN B16 IOSTANDARD LVCMOS33} [get_ports {host_pass}]  ;# IO_L10N_T1_AD11N_15

# Debug header J4 (bank 34)
set_property -dict {PACKAGE_PIN M1  IOSTANDARD LVCMOS33} [get_ports {dbg[0]}]  ;# IO_L2N_T0_34
set_property -dict {PACKAGE_PIN N1  IOSTANDARD LVCMOS33} [get_ports {dbg[1]}]  ;# IO_L4P_T0_34
set_property -dict {PACKAGE_PIN P1  IOSTANDARD LVCMOS33} [get_ports {dbg[2]}]  ;# IO_L4N_T0_34
set_property -dict {PACKAGE_PIN R1  IOSTANDARD LVCMOS33} [get_ports {dbg[3]}]  ;# IO_L7N_T1_34
set_property -dict {PACKAGE_PIN R2  IOSTANDARD LVCMOS33} [get_ports {dbg[4]}]  ;# IO_L7P_T1_34
set_property -dict {PACKAGE_PIN T2  IOSTANDARD LVCMOS33} [get_ports {dbg[5]}]  ;# IO_L8N_T1_34
set_property -dict {PACKAGE_PIN T3  IOSTANDARD LVCMOS33} [get_ports {dbg[6]}]  ;# IO_L9N_T1_DQS_34
set_property -dict {PACKAGE_PIN T4  IOSTANDARD LVCMOS33} [get_ports {dbg[7]}]  ;# IO_L9P_T1_DQS_34

# User LEDs (active high) and button (active low, external 4.7k pull-up), bank 15
set_property -dict {PACKAGE_PIN C16 IOSTANDARD LVCMOS33} [get_ports {led[0]}]  ;# IO_L10P_T1_AD11P_15
set_property -dict {PACKAGE_PIN D16 IOSTANDARD LVCMOS33} [get_ports {led[1]}]  ;# IO_L17N_T2_A25_15
set_property -dict {PACKAGE_PIN E16 IOSTANDARD LVCMOS33} [get_ports {btn_n}]  ;# IO_L17P_T2_A26_15

# Config flash data pins (bank 14). Only needed if your design reads the flash after
# configuration. FLASH_CLK is CCLK: reach it through the STARTUPE2 primitive, not a port.
# set_property -dict {PACKAGE_PIN L12 IOSTANDARD LVCMOS33} [get_ports {flash_cs_n}]  ;# IO_L6P_T0_FCS_B_14
# set_property -dict {PACKAGE_PIN J13 IOSTANDARD LVCMOS33} [get_ports {flash_dq[0]}]  ;# IO_L1P_T0_D00_MOSI_14
# set_property -dict {PACKAGE_PIN J14 IOSTANDARD LVCMOS33} [get_ports {flash_dq[1]}]  ;# IO_L1N_T0_D01_DIN_14
# set_property -dict {PACKAGE_PIN K15 IOSTANDARD LVCMOS33} [get_ports {flash_dq[2]}]  ;# IO_L2P_T0_D02_14
# set_property -dict {PACKAGE_PIN K16 IOSTANDARD LVCMOS33} [get_ports {flash_dq[3]}]  ;# IO_L2N_T0_D03_14
